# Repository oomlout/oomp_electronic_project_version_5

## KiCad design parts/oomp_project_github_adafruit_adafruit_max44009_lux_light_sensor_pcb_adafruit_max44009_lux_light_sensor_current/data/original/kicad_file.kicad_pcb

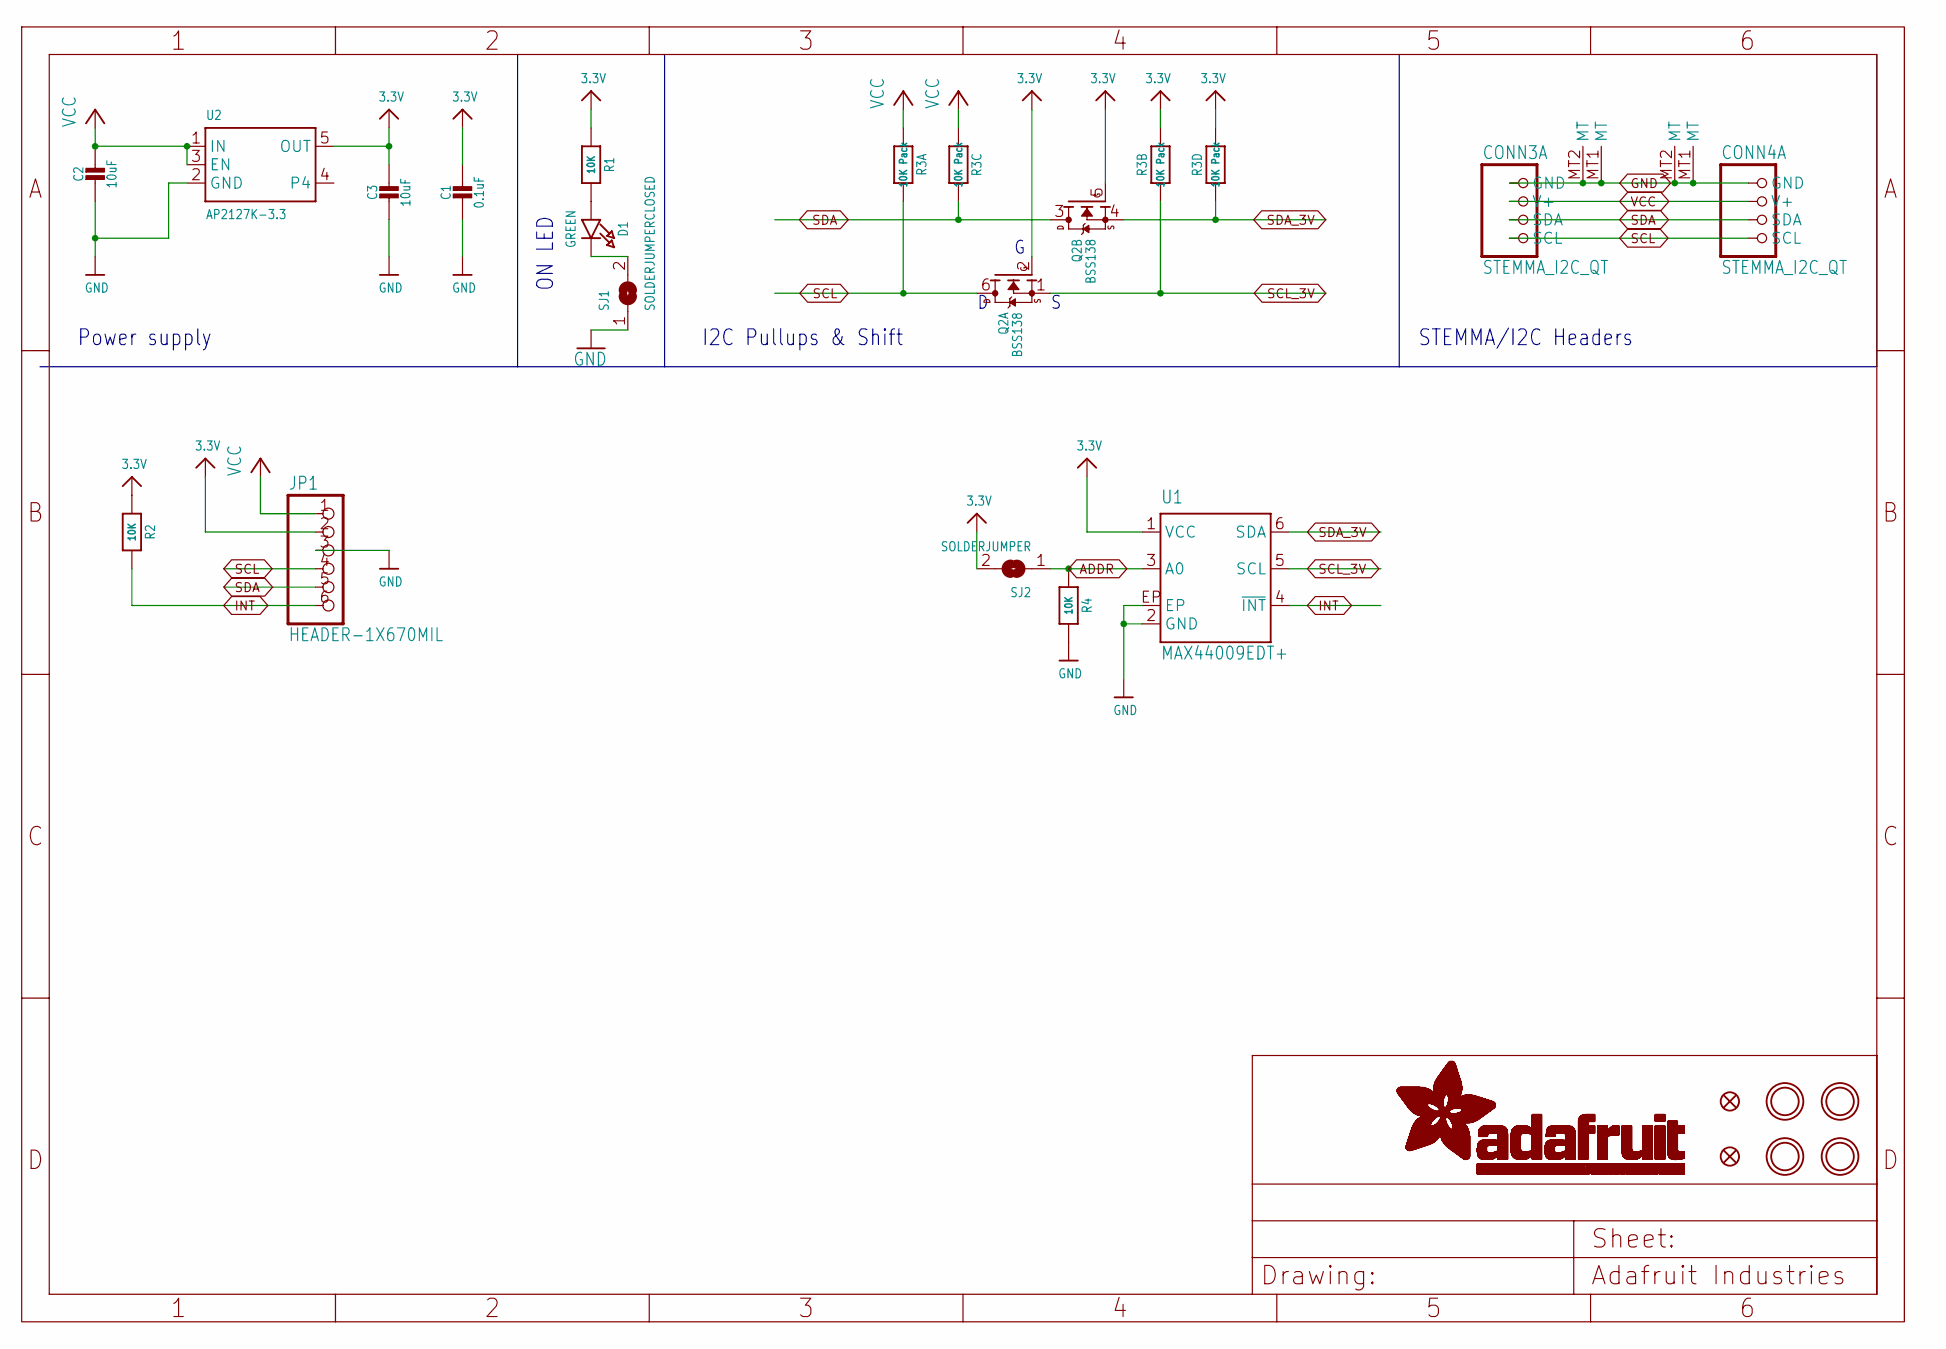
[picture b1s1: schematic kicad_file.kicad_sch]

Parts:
C1: 0.1uF; 0603-NO
C2, C3: 10uF; 0805-NO
CONN3, CONN4: STEMMA_I2C_QT; JST_SH4; LCSC C2845363
D1: GREEN; CHIPLED_0603_NOOUTLINE
FID3, FID4: FIDUCIAL_0.5MM
JP1: HEADER-1X670MIL; 1X06_ROUND_70
Q2: BSS138; SOT363; JLC_ROTATION 270
R1, R2, R4: 10K; 0603-NO
R3: 10K Pack; RESPACK_4X0603
SJ1: SOLDERJUMPERCLOSED; SOLDERJUMPER_CLOSEDWIRE
SJ2: SOLDERJUMPER; SOLDERJUMPER_ARROW_NOPASTE
U1: MAX44009EDT+; UTDFN-OPTO-6
U2: AP2127K-3.3; SOT23-5; JLC_ROTATION 270
U$1, U$17, U$19, U$21: MOUNTINGHOLE2.5; MOUNTINGHOLE_2.5_PLATED

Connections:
3.3V: C1.1, C3.1, JP1.2, Q2.2 (G), Q2.5 (G), R1.1, R2.1, R3.2 (1), R3.4 (1), SJ2.2, U1.1 (VCC), U2.5 (OUT)
ADDR: R4.1, SJ2.1, U1.3 (A0)
GND: C1.2, C2.2, C3.2, CONN3.1 (GND), CONN3.MT1 (MT), CONN3.MT2 (MT), CONN4.1 (GND), CONN4.MT1 (MT), CONN4.MT2 (MT), JP1.3, R4.2, SJ1.1, U1.2 (GND), U1.EP, U2.2 (GND)
INT: JP1.6, R2.2, U1.4 (~INT)
unnamed: D1.A, R1.2
unnamed: D1.C, SJ1.2
SCL: CONN3.4 (SCL), CONN4.4 (SCL), JP1.4, Q2.6 (D), R3.8 (2)
SCL_3V: Q2.1 (S), R3.7 (2), U1.5 (SCL)
SDA: CONN3.3 (SDA), CONN4.3 (SDA), JP1.5, Q2.3 (D), R3.6 (2)
SDA_3V: Q2.4 (S), R3.5 (2), U1.6 (SDA)
VCC: C2.1, CONN3.2 (V+), CONN4.2 (V+), JP1.1, R3.1, R3.3 (1), U2.1 (IN), U2.3 (EN)

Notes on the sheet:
STEMMA/I2C Headers
I2C Pullups & Shift
Power supply
ON LED

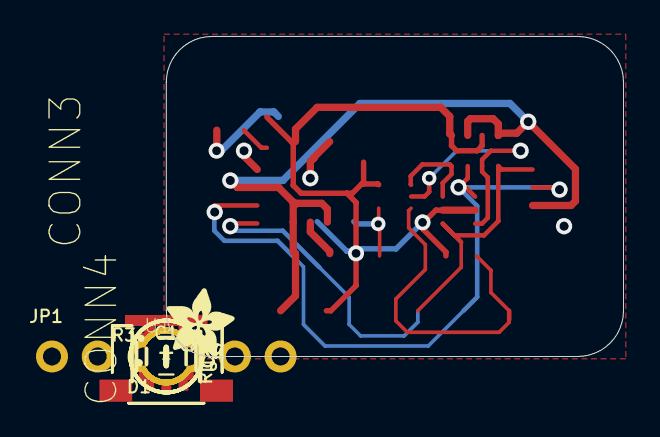
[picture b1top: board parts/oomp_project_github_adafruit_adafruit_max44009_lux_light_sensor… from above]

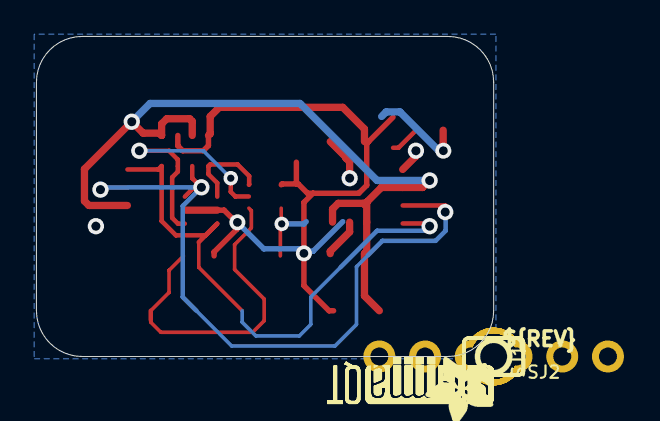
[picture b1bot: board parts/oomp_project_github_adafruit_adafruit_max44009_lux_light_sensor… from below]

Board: 2 copper layers, 25.4 x 17.8 mm, 43 parts (13 on the bottom side), 11 nets.

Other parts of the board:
PLABEL0: PLABEL0
PLABEL1: PLABEL1
PLABEL2: PLABEL2
PLABEL3: PLABEL3
PLABEL4: PLABEL4
PLABEL5: PLABEL5
PLABEL8: PLABEL8
PLABEL13: PLABEL13
PLABEL14: PLABEL14
PLABEL15: PLABEL15
PLABEL16: PLABEL16
PLABEL17: PLABEL17
PLABEL18: PLABEL18
PLABEL19: PLABEL19
PLABEL20: PLABEL20
PLABEL21: PLABEL21
U$2, U$22: ADAFRUIT_3.5MM
U$25: PCBFEAT-REV-040
U$30, U$31: STEMMAQT

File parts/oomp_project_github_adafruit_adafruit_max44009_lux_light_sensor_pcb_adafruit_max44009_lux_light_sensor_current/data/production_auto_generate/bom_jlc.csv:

Comment,Designator,Footprint,LCSC Part #
,JP1,Adafruit MAX44009 Lux Light Sensor-import-fps:1X06_ROUND_70,C37208
,"U$2,U$22",Adafruit MAX44009 Lux Light Sensor-import-fps:ADAFRUIT_3.5MM,
,U$25,Adafruit MAX44009 Lux Light Sensor-import-fps:PCBFEAT-REV-040,
,PLABEL0,Adafruit MAX44009 Lux Light Sensor-import-fps:PLABEL0,
,PLABEL1,Adafruit MAX44009 Lux Light Sensor-import-fps:PLABEL1,
,PLABEL13,Adafruit MAX44009 Lux Light Sensor-import-fps:PLABEL13,
,PLABEL14,Adafruit MAX44009 Lux Light Sensor-import-fps:PLABEL14,
,PLABEL15,Adafruit MAX44009 Lux Light Sensor-import-fps:PLABEL15,
,PLABEL16,Adafruit MAX44009 Lux Light Sensor-import-fps:PLABEL16,
,PLABEL17,Adafruit MAX44009 Lux Light Sensor-import-fps:PLABEL17,
,PLABEL18,Adafruit MAX44009 Lux Light Sensor-import-fps:PLABEL18,
,PLABEL19,Adafruit MAX44009 Lux Light Sensor-import-fps:PLABEL19,
,PLABEL2,Adafruit MAX44009 Lux Light Sensor-import-fps:PLABEL2,
,PLABEL20,Adafruit MAX44009 Lux Light Sensor-import-fps:PLABEL20,
,PLABEL21,Adafruit MAX44009 Lux Light Sensor-import-fps:PLABEL21,
,PLABEL3,Adafruit MAX44009 Lux Light Sensor-import-fps:PLABEL3,
,PLABEL4,Adafruit MAX44009 Lux Light Sensor-import-fps:PLABEL4,
,PLABEL5,Adafruit MAX44009 Lux Light Sensor-import-fps:PLABEL5,
,PLABEL8,Adafruit MAX44009 Lux Light Sensor-import-fps:PLABEL8,
,"U$30,U$31",Adafruit MAX44009 Lux Light Sensor-import-fps:STEMMAQT,
0.1uF,C1,Adafruit MAX44009 Lux Light Sensor-import-fps:0603-NO,C14663
10K,"R1,R2,R4",Adafruit MAX44009 Lux Light Sensor-import-fps:0603-NO,C98220
10K Pack,R3,Adafruit MAX44009 Lux Light Sensor-import-fps:RESPACK_4X0603,C98220
10uF,"C2,C3",Adafruit MAX44009 Lux Light Sensor-import-fps:0805-NO,
AP2127K-3.3,U2,Adafruit MAX44009 Lux Light Sensor-import-fps:SOT23-5,
BSS138,Q2,Adafruit MAX44009 Lux Light Sensor-import-fps:SOT363,
GREEN,D1,Adafruit MAX44009 Lux Light Sensor-import-fps:CHIPLED_0603_NOOUTLINE,
MAX44009EDT+,U1,Adafruit MAX44009 Lux Light Sensor-import-fps:UTDFN-OPTO-6,
STEMMA_I2C_QT,"CONN3,CONN4",Adafruit MAX44009 Lux Light Sensor-import-fps:JST_SH4,C160404

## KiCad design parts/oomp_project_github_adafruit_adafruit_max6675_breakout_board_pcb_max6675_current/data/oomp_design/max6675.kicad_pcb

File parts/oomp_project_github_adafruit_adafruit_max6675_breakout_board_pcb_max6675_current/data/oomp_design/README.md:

# OOMP KiCad design copy

Open `max6675.kicad_pro` (or the `.kicad_pcb` / `.kicad_sch`) in KiCad. Local OOMP libraries are under `libraries/`. Original inputs are preserved in [../original/](../original/).

Only verified unchanged installed KiCad defaults were renamed. Modified, custom, unmatched and unavailable items remain unchanged. Soldering variants are never swapped during conversion. Existing pad coordinates, nets and UUIDs are preserved.

See [conversion_report.yaml](conversion_report.yaml) for every conversion and skip. Copy this directory before editing; regeneration refuses to overwrite edited design files.

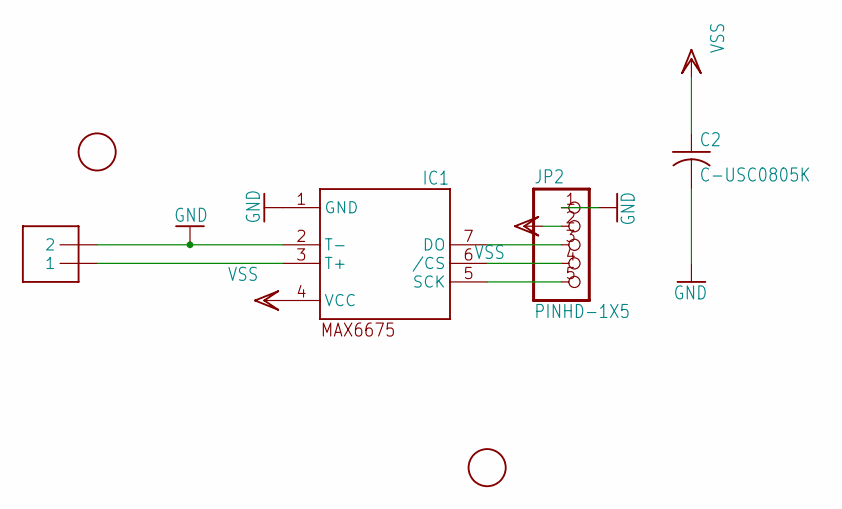
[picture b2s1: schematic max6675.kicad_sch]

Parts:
C2: C-USC0805K; C0805K
IC1: MAX6675; SO08
J1: 1X2-3.5MM; 3.5MMTERM
JP2: PINHD-1X5; 1X05
U$1, U$2: FIDUCIAL; FIDUCIAL_1MM

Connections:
CS: IC1.6 (/CS), JP2.4
CSK: IC1.5 (SCK), JP2.5
DO: IC1.7 (DO), JP2.3
GND: C2.2, IC1.1 (GND), IC1.2 (T-), J1.2, JP2.1
unnamed: IC1.3 (T+), J1.1
VSS: C2.1, IC1.4 (VCC), JP2.2

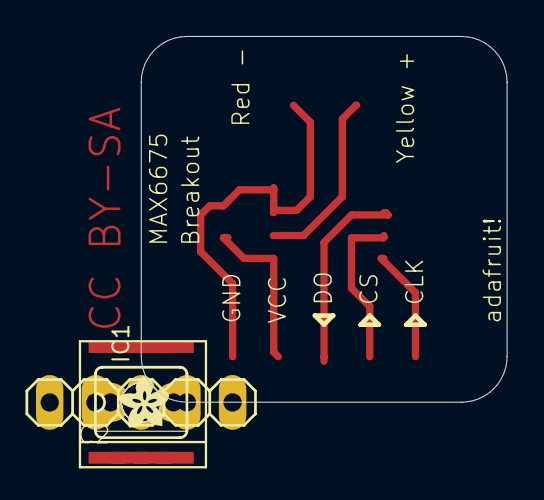
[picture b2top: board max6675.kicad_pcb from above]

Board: 16 copper layers, 20.3 x 20.3 mm, 11 parts (0 on the bottom side), 6 nets.

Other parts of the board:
U$3: ADAFRUIT200MIL
UNK_HOLE_0: dummyfp0
UNK_HOLE_1: dummyfp1
UNK_HOLE_2: dummyfp2
UNK_HOLE_3: dummyfp3

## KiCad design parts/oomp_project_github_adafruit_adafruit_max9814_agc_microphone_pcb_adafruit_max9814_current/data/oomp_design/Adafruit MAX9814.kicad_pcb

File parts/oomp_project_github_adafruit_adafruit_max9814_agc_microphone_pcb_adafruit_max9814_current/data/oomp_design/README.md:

# OOMP KiCad design copy

Open `Adafruit MAX9814.kicad_pro` (or the `.kicad_pcb` / `.kicad_sch`) in KiCad. Local OOMP libraries are under `libraries/`. Original inputs are preserved in [../original/](../original/).

Only verified unchanged installed KiCad defaults were renamed. Modified, custom, unmatched and unavailable items remain unchanged. Soldering variants are never swapped during conversion. Existing pad coordinates, nets and UUIDs are preserved.

See [conversion_report.yaml](conversion_report.yaml) for every conversion and skip. Copy this directory before editing; regeneration refuses to overwrite edited design files.

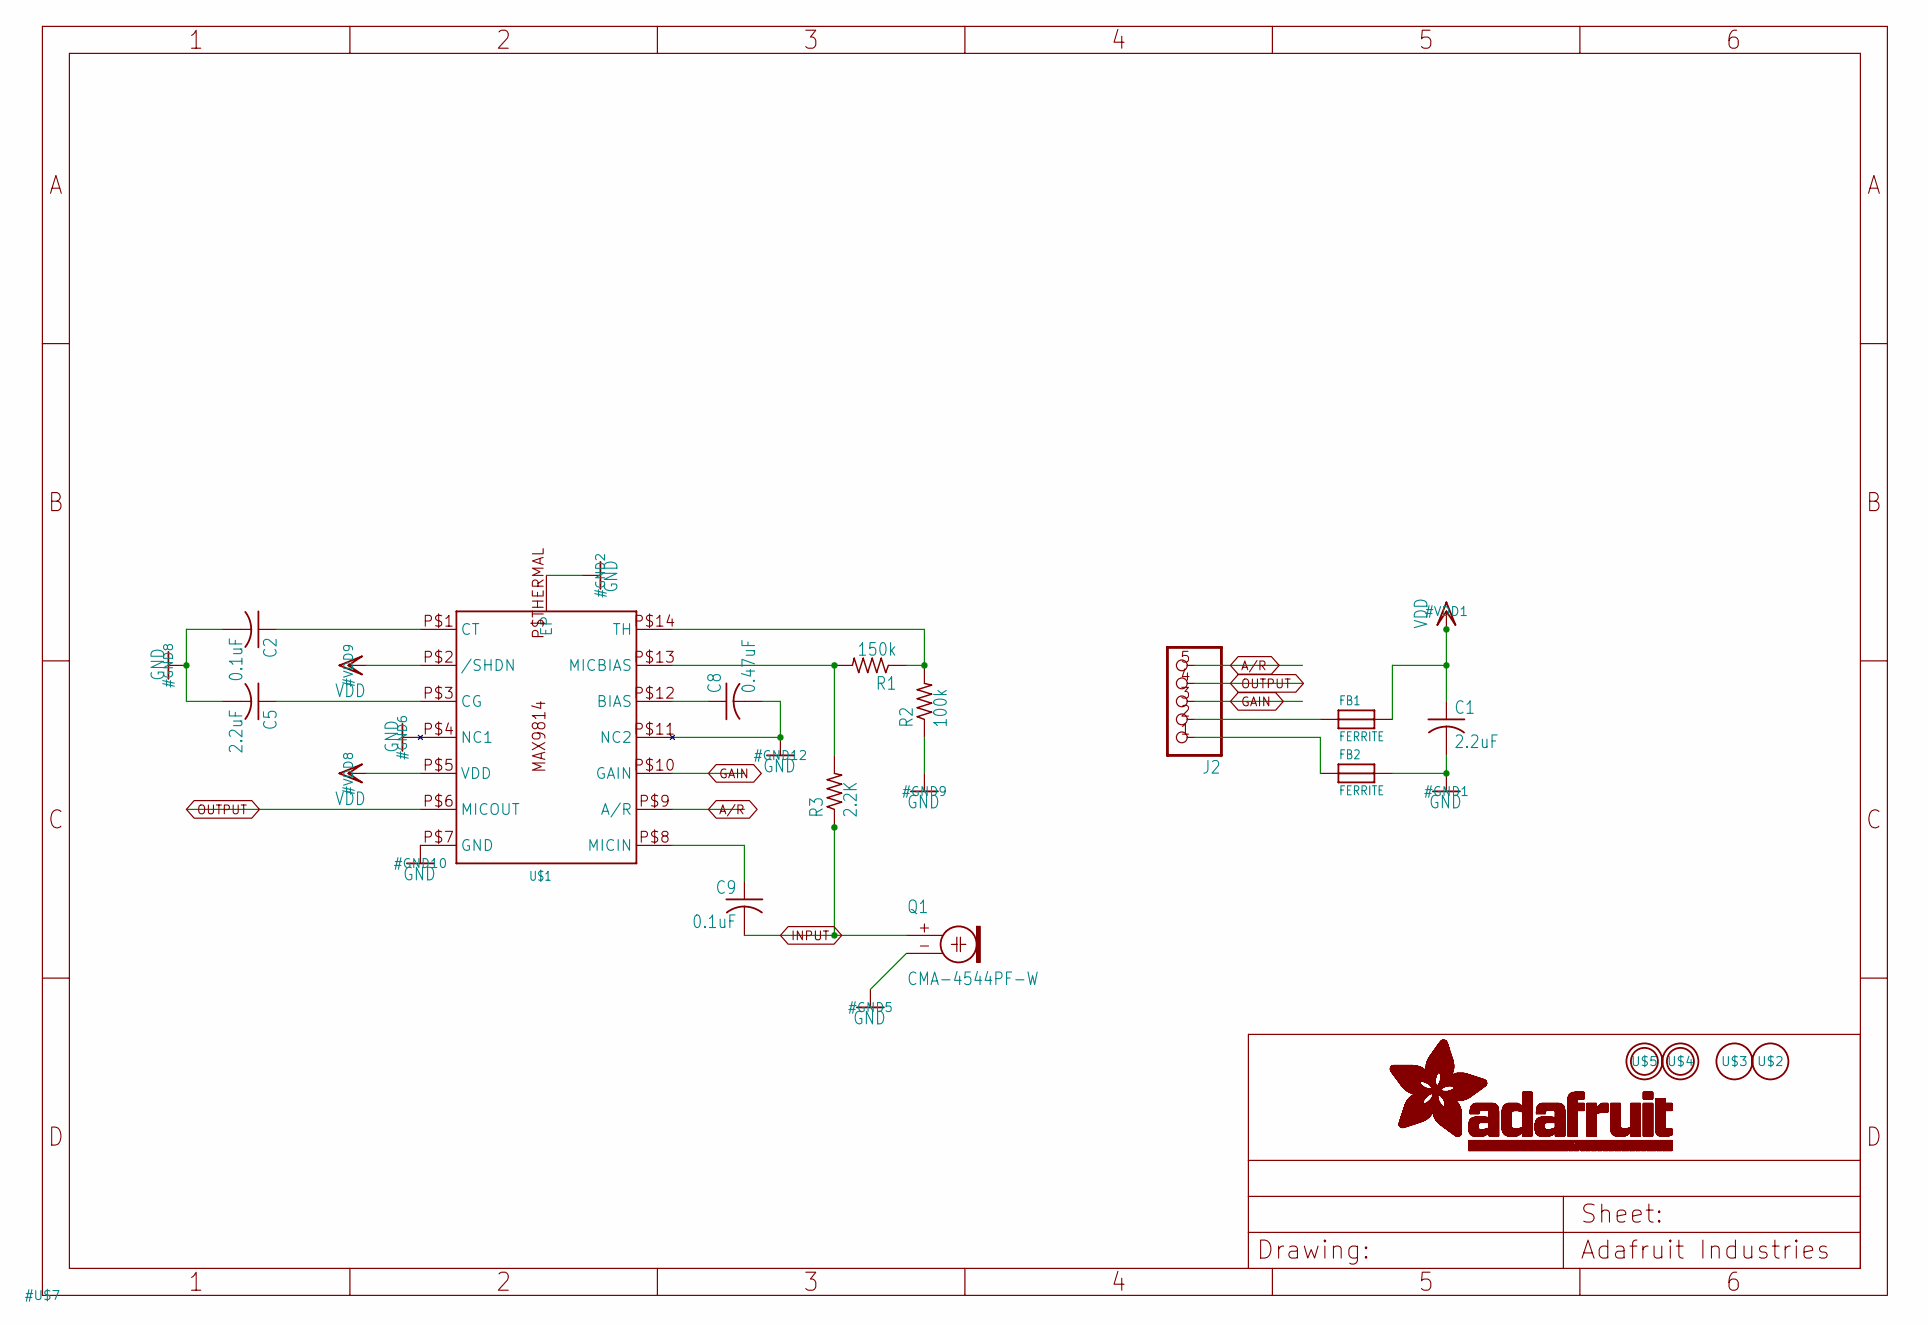
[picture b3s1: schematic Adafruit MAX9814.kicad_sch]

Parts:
C1, C5: 2.2uF; C0805K
C2, C9: 0.1uF; C0805K
C8: 0.47uF; C0805K
FB1, FB2: FERRITE; 0805
J2: HEADER-1X576MIL; 1X05_ROUND_76
Q1: CMA-4544PF-W; 9.7ELECTRET
R1: 150k; R0805
R2: 100k; R0805
R3: 2.2K; R0805
U$1: MAX9814TDFN14; TDFN14_3X3MM
U$2, U$3: FIDUCIAL; FIDUCIAL_1MM
U$4, U$5: MOUNTINGHOLE2.0; MOUNTINGHOLE_2.0_PLATED

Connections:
A/R: J2.5, U$1.P$9 (A/R)
GAIN: J2.3, U$1.P$10 (GAIN)
GND: C1.2, C2.2, C5.2, C8.2, FB2.2, Q1.- (1), R2.1, U$1.P$4 (NC1), U$1.P$7 (GND), U$1.P$11 (NC2), U$1.P$THERMAL (EP)
INPUT: C9.2, Q1.+ (2), R3.1
unnamed: FB1.1, J2.2
unnamed: FB2.1, J2.1
unnamed: C9.1, U$1.P$8 (MICIN)
unnamed: C8.1, U$1.P$12 (BIAS)
unnamed: C2.1, U$1.P$1 (CT)
unnamed: C5.1, U$1.P$3 (CG)
unnamed: R1.1, R2.2, U$1.P$14 (TH)
unnamed: R1.2, R3.2, U$1.P$13 (MICBIAS)
OUTPUT: J2.4, U$1.P$6 (MICOUT)
VDD: C1.1, FB1.2, U$1.P$2 (/SHDN), U$1.P$5 (VDD)

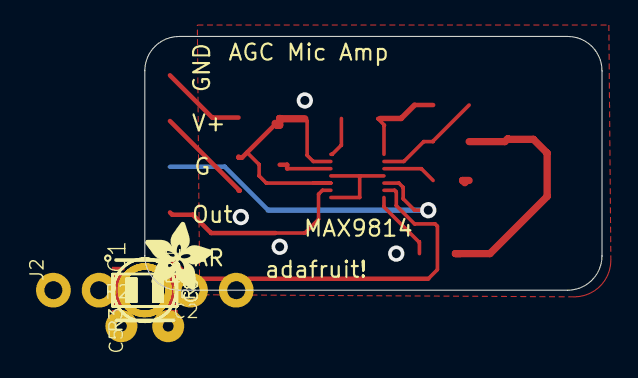
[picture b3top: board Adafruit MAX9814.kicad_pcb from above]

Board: 16 copper layers, 25.4 x 14.1 mm, 18 parts (1 on the bottom side), 14 nets.

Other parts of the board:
U$6: ADAFRUIT_3.5MM

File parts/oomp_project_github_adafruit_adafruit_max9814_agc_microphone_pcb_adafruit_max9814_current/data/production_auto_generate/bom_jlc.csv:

Comment,Designator,Footprint,LCSC Part #
,J2,Adafruit MAX9814-import-fps:1X05_ROUND_76,C42431835
,U$6,Adafruit MAX9814-import-fps:ADAFRUIT_3.5MM,
0.1uF,"C2,C9",Adafruit MAX9814-import-fps:C0805K,
0.47uF,C8,Adafruit MAX9814-import-fps:C0805K,
100k,R2,Adafruit MAX9814-import-fps:R0805,C149504
150k,R1,Adafruit MAX9814-import-fps:R0805,C2907228
2.2K,R3,Adafruit MAX9814-import-fps:R0805,C17520
2.2uF,"C1,C5",Adafruit MAX9814-import-fps:C0805K,
CMA-4544PF-W,Q1,Adafruit MAX9814-import-fps:9.7ELECTRET,
FERRITE,"FB1,FB2",Adafruit MAX9814-import-fps:0805,
FIDUCIAL,"U$2,U$3",Adafruit MAX9814-import-fps:FIDUCIAL_1MM,
MAX9814TDFN14,U$1,Adafruit MAX9814-import-fps:TDFN14_3X3MM,

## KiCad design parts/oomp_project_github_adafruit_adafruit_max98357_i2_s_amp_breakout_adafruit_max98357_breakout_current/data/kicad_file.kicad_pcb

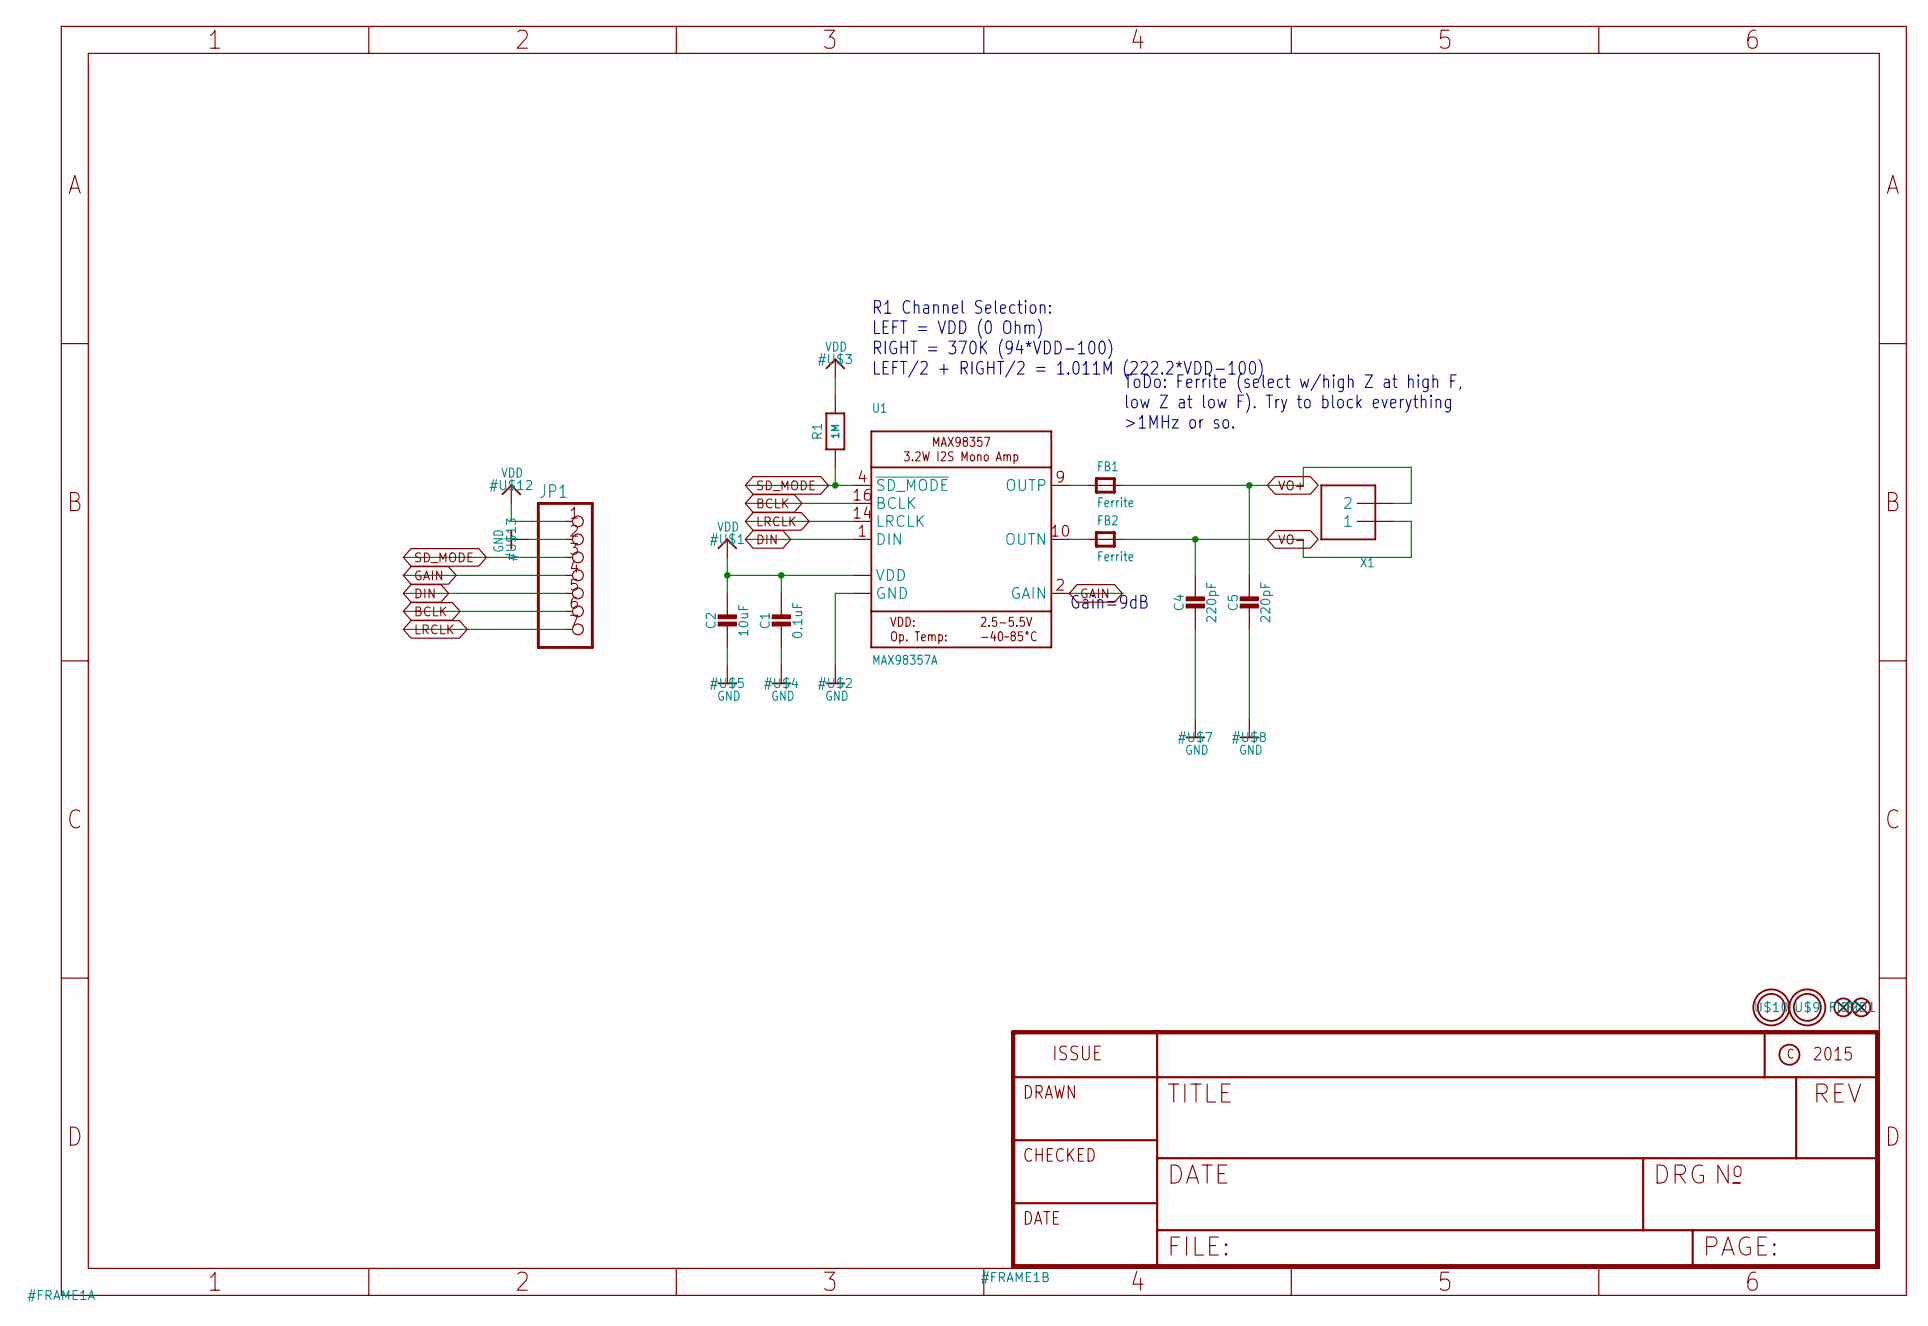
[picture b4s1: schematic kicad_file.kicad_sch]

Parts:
C1: 0.1uF; 0805-NO
C2: 10uF; 0805-NO
C4, C5: 220pF; 0805-NO
FB1, FB2: Ferrite; 0805-NO
FID1, FID2: FIDUCIAL""; FIDUCIAL_1MM
JP1: HEADER-1X7THICKER; 1X07_ROUND_76
R1: 1M; 0805-NO
U1: MAX98357A; QFN16_3MM
U$9, U$10: MOUNTINGHOLE2.5; MOUNTINGHOLE_2.5_PLATED
X1: TERMBLOCK_1X2; TERMBLOCK_1X2-3.5MM

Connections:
BCLK: JP1.6, U1.16 (BCLK)
DIN: JP1.5, U1.1 (DIN)
GAIN: JP1.4, U1.2 (GAIN)
GND: C1.2, C2.2, C4.2, C5.2, JP1.2, U1.3 (GND), U1.11 (GND), U1.15 (GND), U1.THERMAL (GND)
LRCLK: JP1.7, U1.14 (LRCLK)
unnamed: FB2.1, U1.10 (OUTN)
unnamed: FB1.1, U1.9 (OUTP)
SD_MODE: JP1.3, R1.1, U1.4 (~SD_MODE)
VDD: C1.1, C2.1, JP1.1, R1.2, U1.7 (VDD), U1.8 (VDD)
VO+: C5.1, FB1.2, X1.2
VO-: C4.1, FB2.2, X1.1

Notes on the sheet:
Gain=9dB
ToDo: Ferrite (select w/high Z at high F, low Z at low F). Try to block everything >1MHz or so.
R1 Channel Selection: LEFT = VDD (0 Ohm) RIGHT = 370K (94*VDD-100) LEFT/2 + RIGHT/2 = 1.011M (222.2*VDD-100)

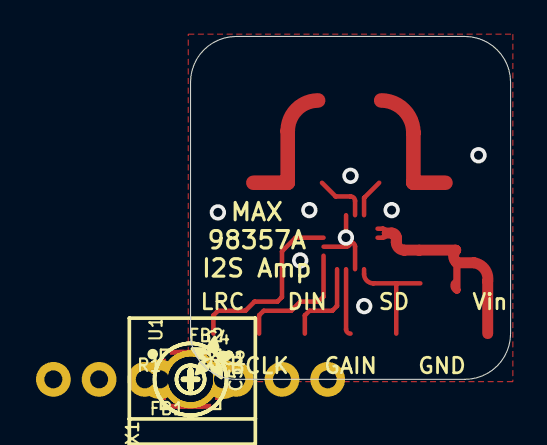
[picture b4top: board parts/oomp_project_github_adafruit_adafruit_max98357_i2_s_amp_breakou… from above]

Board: 2 copper layers, 17.8 x 19.1 mm, 18 parts (1 on the bottom side), 11 nets.

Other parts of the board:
U$6: SYMBOL_PLUS
U$11: SYMBOL_MINUS
U$14: ADAFRUIT_2.5MM
U$15: PCBFEAT-REV-040

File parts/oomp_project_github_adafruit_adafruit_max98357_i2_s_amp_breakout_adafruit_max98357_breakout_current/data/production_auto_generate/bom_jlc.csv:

Comment,Designator,Footprint,LCSC Part #
,JP1,Adafruit MAX98357 Breakout-import-fps:1X07_ROUND_76,C7501585
,U$14,Adafruit MAX98357 Breakout-import-fps:ADAFRUIT_2.5MM,
,U$15,Adafruit MAX98357 Breakout-import-fps:PCBFEAT-REV-040,
,U$11,Adafruit MAX98357 Breakout-import-fps:SYMBOL_MINUS,
,U$6,Adafruit MAX98357 Breakout-import-fps:SYMBOL_PLUS,
,X1,Adafruit MAX98357 Breakout-import-fps:TERMBLOCK_1X2-3.5MM,
0.1uF,C1,Adafruit MAX98357 Breakout-import-fps:0805-NO,
10uF,C2,Adafruit MAX98357 Breakout-import-fps:0805-NO,
1M,R1,Adafruit MAX98357 Breakout-import-fps:0805-NO,C2933280
220pF,"C4,C5",Adafruit MAX98357 Breakout-import-fps:0805-NO,
Ferrite,"FB1,FB2",Adafruit MAX98357 Breakout-import-fps:0805-NO,
MAX98357A,U1,Adafruit MAX98357 Breakout-import-fps:QFN16_3MM,

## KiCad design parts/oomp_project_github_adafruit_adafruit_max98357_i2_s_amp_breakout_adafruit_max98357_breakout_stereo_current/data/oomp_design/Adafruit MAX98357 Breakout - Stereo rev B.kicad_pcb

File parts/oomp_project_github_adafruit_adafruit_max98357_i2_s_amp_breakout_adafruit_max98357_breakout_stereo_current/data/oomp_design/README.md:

# OOMP KiCad design copy

Open `Adafruit MAX98357 Breakout - Stereo rev B.kicad_pro` (or the `.kicad_pcb` / `.kicad_sch`) in KiCad. Local OOMP libraries are under `libraries/`. Original inputs are preserved in [../original/](../original/).

Only verified unchanged installed KiCad defaults were renamed. Modified, custom, unmatched and unavailable items remain unchanged. Soldering variants are never swapped during conversion. Existing pad coordinates, nets and UUIDs are preserved.

See [conversion_report.yaml](conversion_report.yaml) for every conversion and skip. Copy this directory before editing; regeneration refuses to overwrite edited design files.

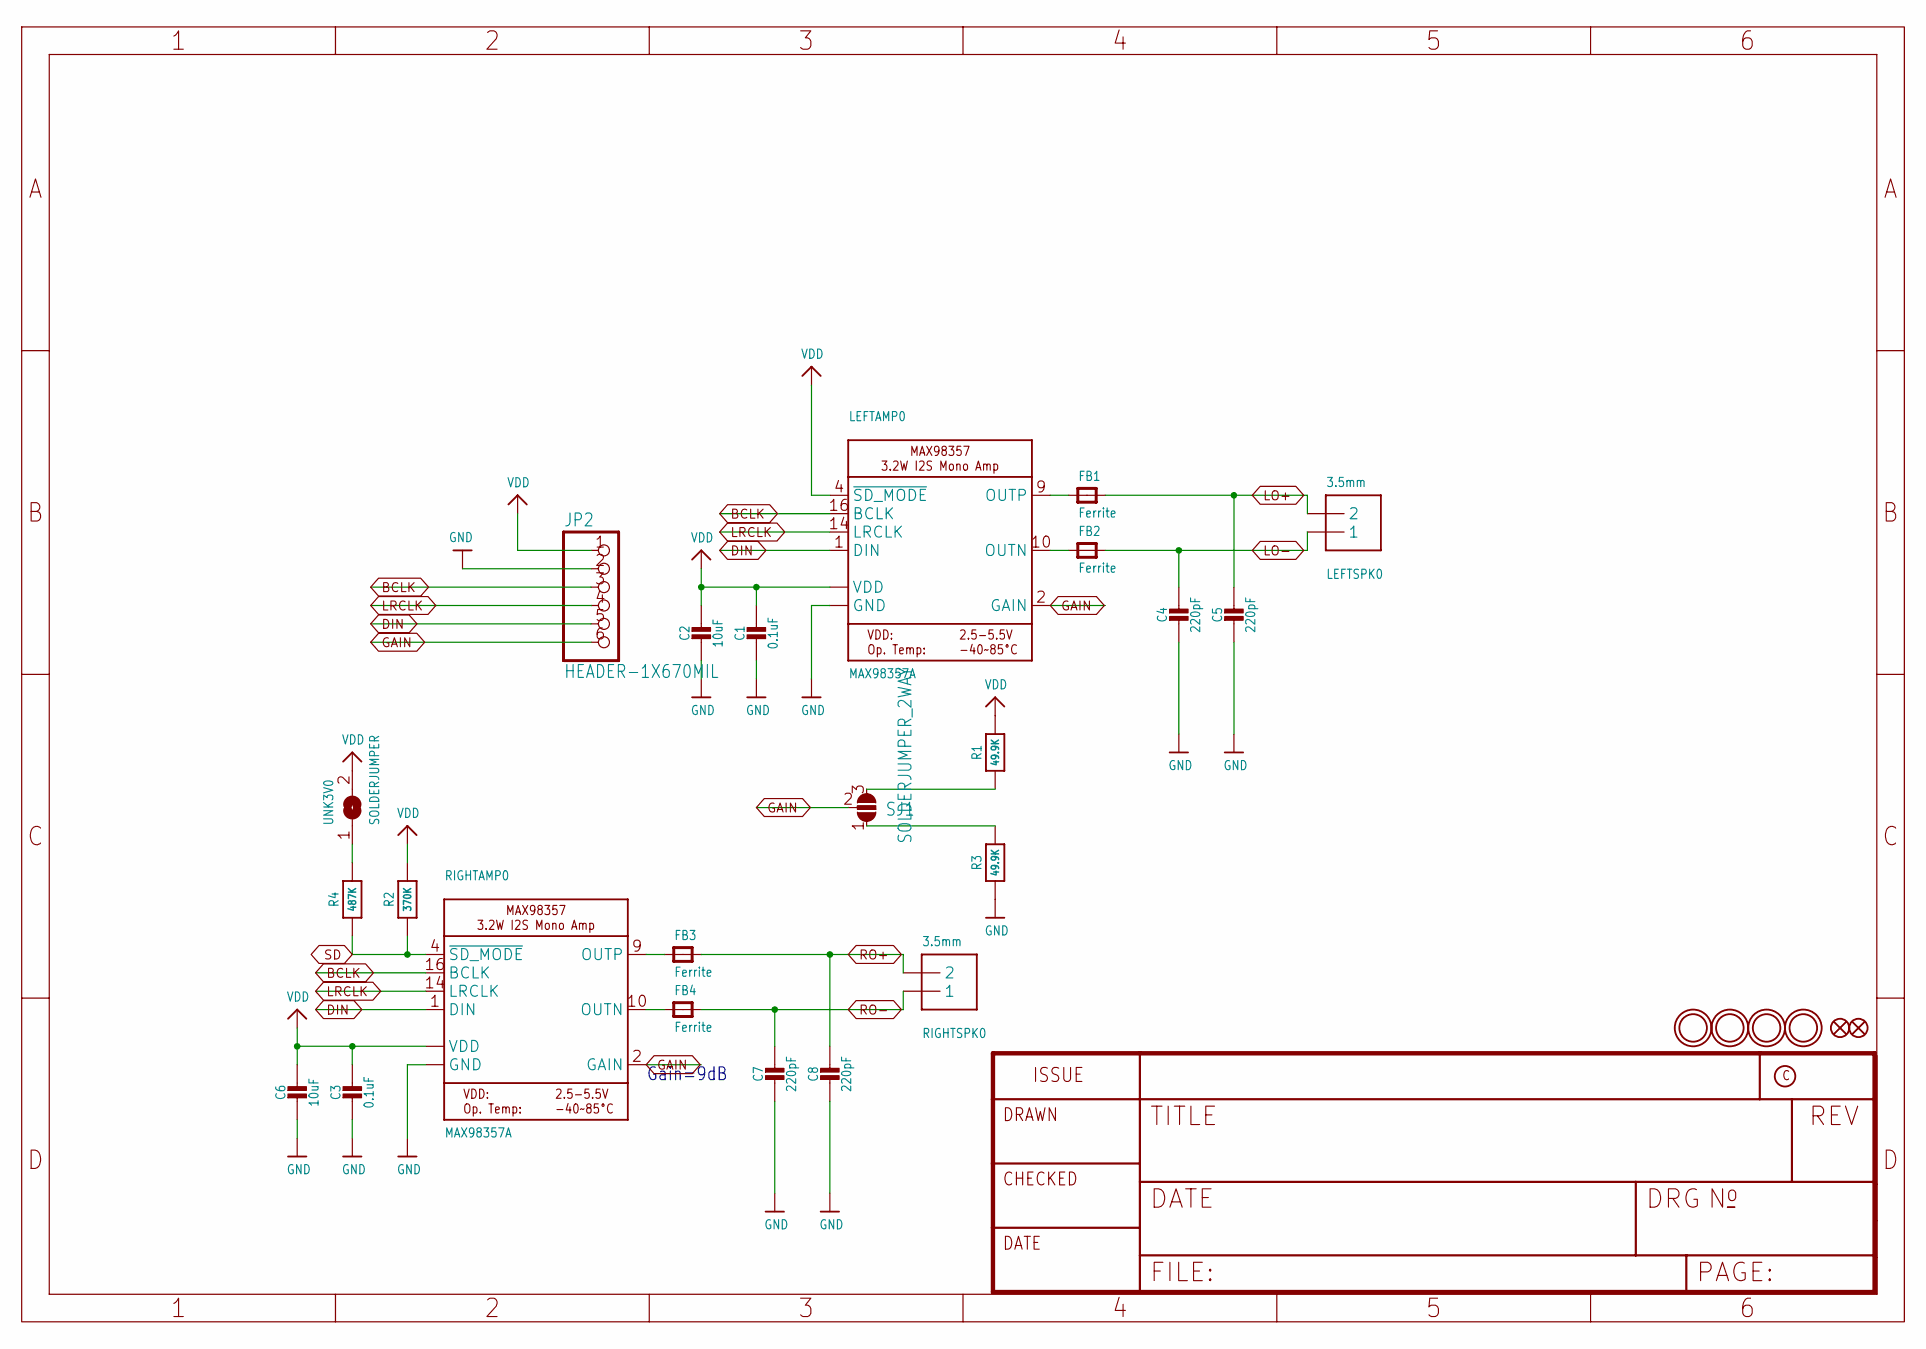
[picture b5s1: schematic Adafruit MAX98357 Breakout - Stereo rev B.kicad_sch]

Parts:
C1, C3: 0.1uF; 0603-NO
C2, C6: 10uF; 0805-NO
C4, C5, C7, C8: 220pF; 0603-NO
FB1, FB2, FB3, FB4: Ferrite; 0603-NO
FID1, FID2: FIDUCIAL_0.5MM
JP2: HEADER-1X670MIL; 1X06_ROUND_70
LEFTAMP0: MAX98357A; QFN16_3MM
LEFTSPK0: 3.5mm; TERMBLOCK_1X2-3.5MM
R1, R3: 49.9K; 0603-NO
R2: 370K; 0603-NO
R4: 487K; 0603-NO
RIGHTAMP0: MAX98357A; QFN16_3MM
RIGHTSPK0: 3.5mm; TERMBLOCK_1X2-3.5MM
SJ1: SOLDERJUMPER_2WAY; SOLDERJUMPER_2WAY_OPEN_NOPASTE
U$9, U$10, U$23, U$24: MOUNTINGHOLE2.5; MOUNTINGHOLE_2.5_PLATED
UNK3V0: SOLDERJUMPER; SOLDERJUMPER_ARROW_NOPASTE

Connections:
BCLK: JP2.3, LEFTAMP0.16 (BCLK), RIGHTAMP0.16 (BCLK)
DIN: JP2.5, LEFTAMP0.1 (DIN), RIGHTAMP0.1 (DIN)
GAIN: JP2.6, LEFTAMP0.2 (GAIN), RIGHTAMP0.2 (GAIN), SJ1.2
GND: C1.2, C2.2, C3.2, C4.2, C5.2, C6.2, C7.2, C8.2, JP2.2, LEFTAMP0.3 (GND), LEFTAMP0.11 (GND), LEFTAMP0.15 (GND), LEFTAMP0.THERMAL (GND), R3.1, RIGHTAMP0.3 (GND), RIGHTAMP0.11 (GND), RIGHTAMP0.15 (GND), RIGHTAMP0.THERMAL (GND)
LO+: C5.1, FB1.2, LEFTSPK0.2
LO-: C4.1, FB2.2, LEFTSPK0.1
LRCLK: JP2.4, LEFTAMP0.14 (LRCLK), RIGHTAMP0.14 (LRCLK)
unnamed: FB4.1, RIGHTAMP0.10 (OUTN)
unnamed: FB3.1, RIGHTAMP0.9 (OUTP)
unnamed: R3.2, SJ1.1
unnamed: R4.2, UNK3V0.1
unnamed: FB2.1, LEFTAMP0.10 (OUTN)
unnamed: FB1.1, LEFTAMP0.9 (OUTP)
unnamed: R1.1, SJ1.3
RO+: C8.1, FB3.2, RIGHTSPK0.2
RO-: C7.1, FB4.2, RIGHTSPK0.1
SD: R2.1, R4.1, RIGHTAMP0.4 (~SD_MODE)
VDD: C1.1, C2.1, C3.1, C6.1, JP2.1, LEFTAMP0.4 (~SD_MODE), LEFTAMP0.7 (VDD), LEFTAMP0.8 (VDD), R1.2, R2.2, RIGHTAMP0.7 (VDD), RIGHTAMP0.8 (VDD), UNK3V0.2

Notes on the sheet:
Gain=9dB

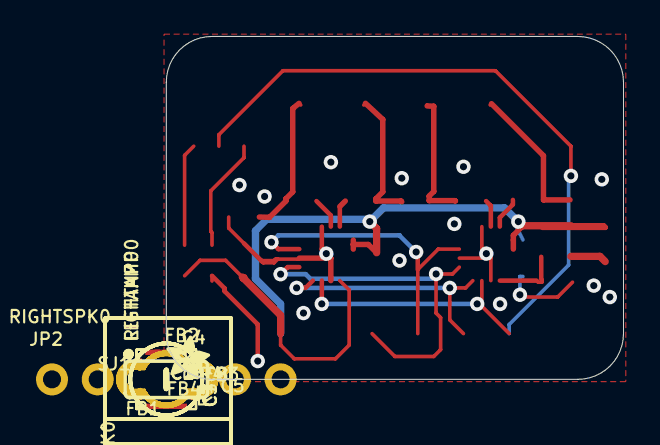
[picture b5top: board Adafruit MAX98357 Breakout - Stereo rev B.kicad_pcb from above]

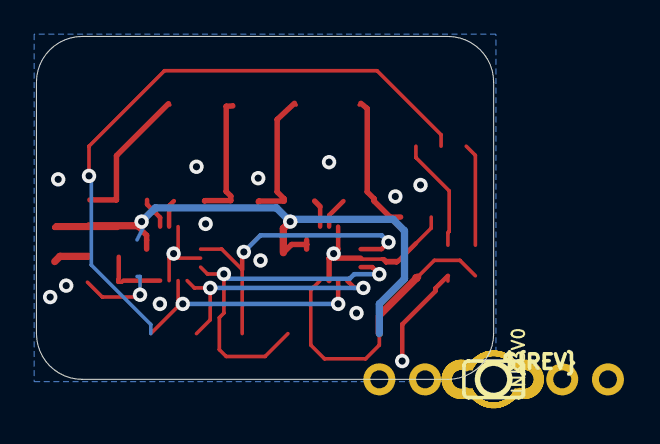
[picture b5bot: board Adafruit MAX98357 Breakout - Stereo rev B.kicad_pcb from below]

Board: 2 copper layers, 25.4 x 19.1 mm, 51 parts (6 on the bottom side), 18 nets.

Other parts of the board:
PLABEL0: PLABEL0
PLABEL1: PLABEL1
PLABEL2: PLABEL2
PLABEL3: PLABEL3
PLABEL4: PLABEL4
PLABEL5: PLABEL5
PLABEL6: PLABEL6
PLABEL7: PLABEL7
PLABEL8: PLABEL8
PLABEL9: PLABEL9
PLABEL10: PLABEL10
PLABEL11: PLABEL11
PLABEL12: PLABEL12
PLABEL13: PLABEL13
PLABEL14: PLABEL14
PLABEL15: PLABEL15
PLABEL16: PLABEL16
PLABEL17: PLABEL17
PLABEL18: PLABEL18
PLABEL19: PLABEL19
U$14: ADAFRUIT_2.5MM
U$15: PCBFEAT-REV-040

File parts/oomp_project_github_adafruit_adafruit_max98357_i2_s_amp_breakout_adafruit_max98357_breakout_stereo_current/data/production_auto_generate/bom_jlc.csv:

Comment,Designator,Footprint,LCSC Part #
,JP2,Adafruit MAX98357 Breakout - Stereo rev B-import-fps:1X06_ROUND_70,C37208
,U$14,Adafruit MAX98357 Breakout - Stereo rev B-import-fps:ADAFRUIT_2.5MM,
,U$15,Adafruit MAX98357 Breakout - Stereo rev B-import-fps:PCBFEAT-REV-040,
,PLABEL0,Adafruit MAX98357 Breakout - Stereo rev B-import-fps:PLABEL0,
,PLABEL1,Adafruit MAX98357 Breakout - Stereo rev B-import-fps:PLABEL1,
,PLABEL10,Adafruit MAX98357 Breakout - Stereo rev B-import-fps:PLABEL10,
,PLABEL11,Adafruit MAX98357 Breakout - Stereo rev B-import-fps:PLABEL11,
,PLABEL12,Adafruit MAX98357 Breakout - Stereo rev B-import-fps:PLABEL12,
,PLABEL13,Adafruit MAX98357 Breakout - Stereo rev B-import-fps:PLABEL13,
,PLABEL14,Adafruit MAX98357 Breakout - Stereo rev B-import-fps:PLABEL14,
,PLABEL15,Adafruit MAX98357 Breakout - Stereo rev B-import-fps:PLABEL15,
,PLABEL16,Adafruit MAX98357 Breakout - Stereo rev B-import-fps:PLABEL16,
,PLABEL17,Adafruit MAX98357 Breakout - Stereo rev B-import-fps:PLABEL17,
,PLABEL18,Adafruit MAX98357 Breakout - Stereo rev B-import-fps:PLABEL18,
,PLABEL19,Adafruit MAX98357 Breakout - Stereo rev B-import-fps:PLABEL19,
,PLABEL2,Adafruit MAX98357 Breakout - Stereo rev B-import-fps:PLABEL2,
,PLABEL3,Adafruit MAX98357 Breakout - Stereo rev B-import-fps:PLABEL3,
,PLABEL4,Adafruit MAX98357 Breakout - Stereo rev B-import-fps:PLABEL4,
,PLABEL5,Adafruit MAX98357 Breakout - Stereo rev B-import-fps:PLABEL5,
,PLABEL6,Adafruit MAX98357 Breakout - Stereo rev B-import-fps:PLABEL6,
,PLABEL7,Adafruit MAX98357 Breakout - Stereo rev B-import-fps:PLABEL7,
,PLABEL8,Adafruit MAX98357 Breakout - Stereo rev B-import-fps:PLABEL8,
,PLABEL9,Adafruit MAX98357 Breakout - Stereo rev B-import-fps:PLABEL9,
,UNK3V0,Adafruit MAX98357 Breakout - Stereo rev B-import-fps:SOLDERJUMPER_ARROW_NOPASTE,
0.1uF,"C1,C3",Adafruit MAX98357 Breakout - Stereo rev B-import-fps:0603-NO,C14663
10uF,"C2,C6",Adafruit MAX98357 Breakout - Stereo rev B-import-fps:0805-NO,
220pF,"C4,C5,C7,C8",Adafruit MAX98357 Breakout - Stereo rev B-import-fps:0603-NO,
3.5mm,"LEFTSPK0,RIGHTSPK0",Adafruit MAX98357 Breakout - Stereo rev B-import-fps:TERMBLOCK_1X2-3.5MM,
370K,R2,Adafruit MAX98357 Breakout - Stereo rev B-import-fps:0603-NO,
487K,R4,Adafruit MAX98357 Breakout - Stereo rev B-import-fps:0603-NO,
49.9K,"R1,R3",Adafruit MAX98357 Breakout - Stereo rev B-import-fps:0603-NO,
Ferrite,"FB1,FB2,FB3,FB4",Adafruit MAX98357 Breakout - Stereo rev B-import-fps:0603-NO,
MAX98357A,"LEFTAMP0,RIGHTAMP0",Adafruit MAX98357 Breakout - Stereo rev B-import-fps:QFN16_3MM,

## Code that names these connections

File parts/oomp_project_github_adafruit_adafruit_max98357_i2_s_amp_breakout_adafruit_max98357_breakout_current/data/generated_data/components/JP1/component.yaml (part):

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        pin_name: '1'
      - reference: U1
        pin_number: '4'
        pin_name: ~{SD_MODE}
    - number: '4'
      name: '4'
      electrical_type: passive
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      connected_to:
      - reference: U1
        pin_number: '2'
        pin_name: GAIN
    - number: '5'
      name: '5'
      electrical_type: passive
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      connected_to:
      - reference: U1
        pin_number: '1'
        pin_name: DIN
    - number: '6'
      name: '6'
      electrical_type: passive
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      connected_to:
      - reference: U1
        pin_number: '16'
        pin_name: BCLK
    - number: '7'
      name: '7'
      electrical_type: passive
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      connected_to:
      - reference: U1
        pin_number: '14'
        pin_name: LRCLK
    size:
      local_graphics:
        measurement: symbol graphics only; excludes pins, properties, and text
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    pin_name: '2'
  - reference: U1
    pin_number: '1'
    pin_name: DIN
  - reference: U1
    pin_number: '11'
    pin_name: GND
  - reference: U1
    pin_number: '14'
    pin_name: LRCLK
  - reference: U1
    pin_number: '15'
    pin_name: GND
  - reference: U1
    pin_number: '16'
    pin_name: BCLK
  - reference: U1
    pin_number: '2'
    pin_name: GAIN
  - reference: U1
    pin_number: '3'
    pin_name: GND
  - reference: U1
    pin_number: '4'
    pin_name: ~{SD_MODE}
  - reference: U1
    pin_number: '7'
    pin_name: VDD
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

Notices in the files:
parts/oomp_project_github_adafruit_adafruit_max6675_breakout_board_pcb_max6675_current/data/oomp_design/max6675.kicad_pcb:
CC BY-SA
